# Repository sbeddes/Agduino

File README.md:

# Agduino
A compact root module system to use with an Arduino Nano, Screw Terminal, RTC 3231, and SD Card module for simple datalogging.

Primarily for use with the Arduino Nano Family. 

The Logger library provides easy device fusion for datalogging using the RTC and SD libraries. While this library can be used for any Arduino IDE cabale board, it was designed to be used with the Arduino Nano family.

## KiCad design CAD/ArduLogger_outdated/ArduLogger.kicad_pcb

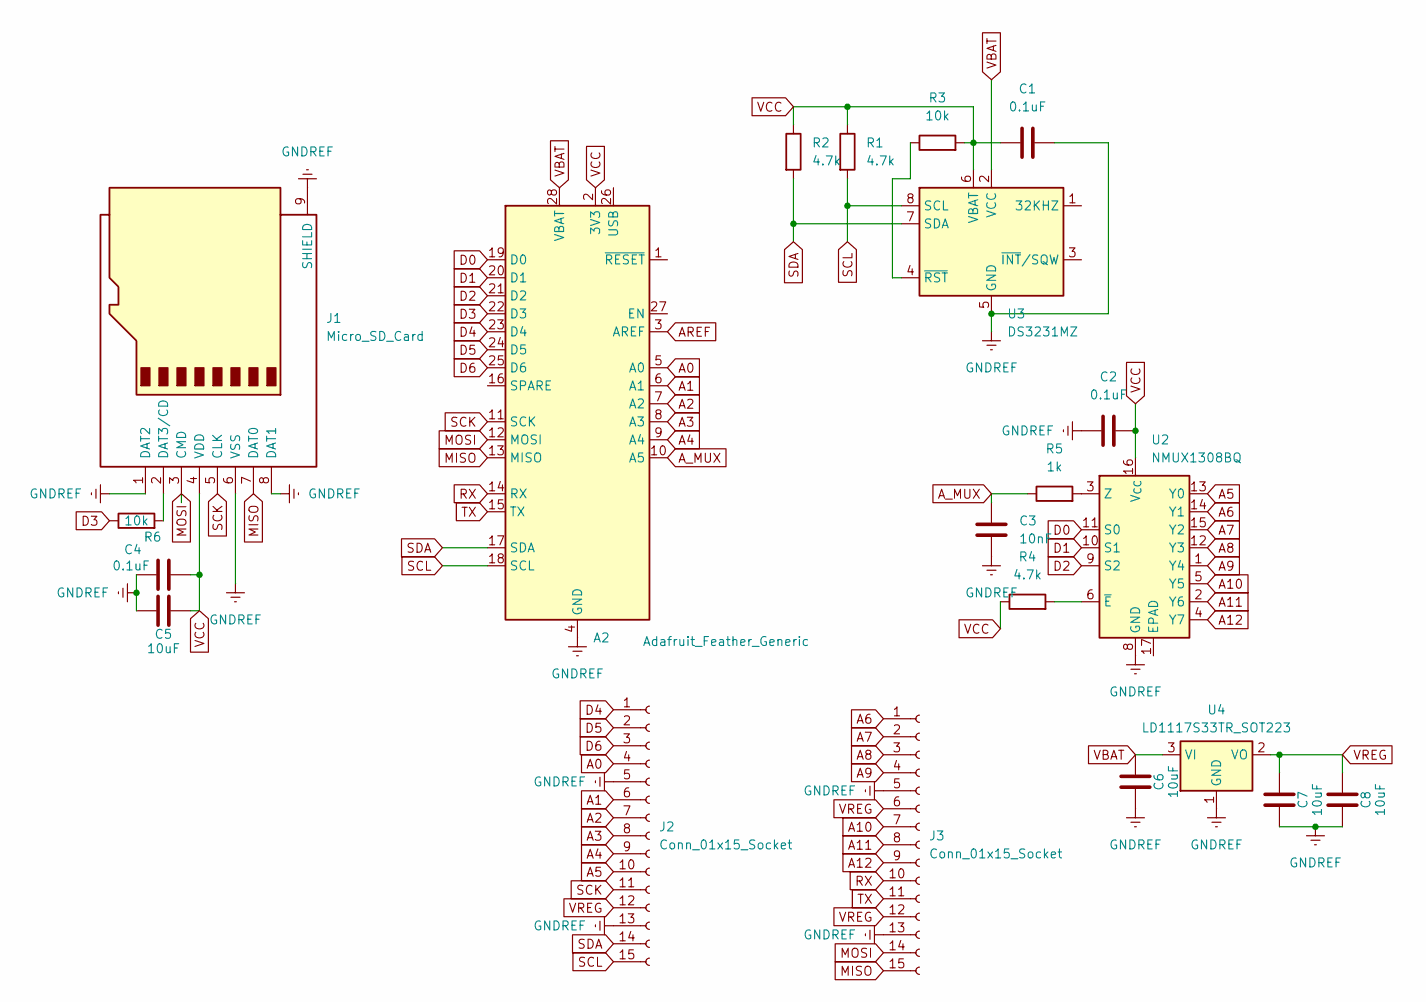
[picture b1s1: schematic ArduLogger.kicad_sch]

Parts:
A2: Adafruit_Feather_Generic; Adafruit_Feather
C1, C2, C4: 0.1uF; C_0603_1608Metric
C3: 10nF; C_0603_1608Metric
C5, C6, C7, C8: 10uF; C_0603_1608Metric
J1: Micro_SD_Card; microSD_HC_Wuerth_693072010801
J2, J3: Conn_01x15_Socket; PhoenixContact_MSTBVA_2,5_15-G-5,08_1x15_P5.08mm_Vertical
R1, R2, R4: 4.7k; R_0603_1608Metric
R3, R6: 10k; R_0603_1608Metric
R5: 1k; R_0603_1608Metric
U2: NMUX1308BQ; DHVQFN-16-1EP_2.5x3.5mm_P0.5mm_EP1x2mm
U3: DS3231MZ; SOIC-8_3.9x4.9mm_P1.27mm
U4: LD1117S33TR_SOT223; SOT-223-3_TabPin2

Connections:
A0: A2.5 (A0), J2.4
A1: A2.6 (A1), J2.6
A2: A2.7 (A2), J2.7
A3: A2.8 (A3), J2.8
A4: A2.9 (A4), J2.9
A5: J2.10, U2.13 (Y0)
A6: J3.1, U2.14 (Y1)
A7: J3.2, U2.15 (Y2)
A8: J3.3, U2.12 (Y3)
A9: J3.4, U2.1 (Y4)
A10: J3.7, U2.5 (Y5)
A11: J3.8, U2.2 (Y6)
A12: J3.9, U2.4 (Y7)
AREF: A2.3 (AREF)
A_MUX: A2.10 (A5), C3.1, R5.1
D0: A2.19 (D0), U2.11 (S0)
D1: A2.20 (D1), U2.10 (S1)
D2: A2.21 (D2), U2.9 (S2)
D3: A2.22 (D3), R6.1
D4: A2.23 (D4), J2.1
D5: A2.24 (D5), J2.2
D6: A2.25 (D6), J2.3
GNDREF: A2.4 (GND), C1.2, C2.1, C3.2, C4.1, C5.1, C6.1, C7.1, C8.1, J1.1 (DAT2), J1.6 (VSS), J1.8 (DAT1), J1.9 (SHIELD), J2.5, J2.13, J3.5, J3.13, U2.8 (GND), U3.5 (GND), U4.1 (GND)
MISO: A2.13 (MISO), J1.7 (DAT0), J3.15
MOSI: A2.12 (MOSI), J1.3 (CMD), J3.14
unnamed: J1.2 (DAT3/CD), R6.2
unnamed: R5.2, U2.3 (Z)
unnamed: R4.2, U2.6 (~E)
unnamed: R3.1, U3.4 (~RST)
RX: A2.14 (RX), J3.10
SCK: A2.11 (SCK), J1.5 (CLK), J2.11
SCL: A2.18 (SCL), J2.15, R1.2, U3.8 (SCL)
SDA: A2.17 (SDA), J2.14, R2.2, U3.7 (SDA)
TX: A2.15 (TX), J3.11
VBAT: A2.28 (VBAT), C6.2, U3.2 (VCC), U4.3 (VI)
VCC: A2.2 (3V3), C1.1, C2.2, C4.2, C5.2, J1.4 (VDD), R1.1, R2.1, R3.2, R4.1, U2.16 (V_{CC}), U3.6 (VBAT)
VREG: C7.2, C8.2, J2.12, J3.6, J3.12, U4.2 (VO)

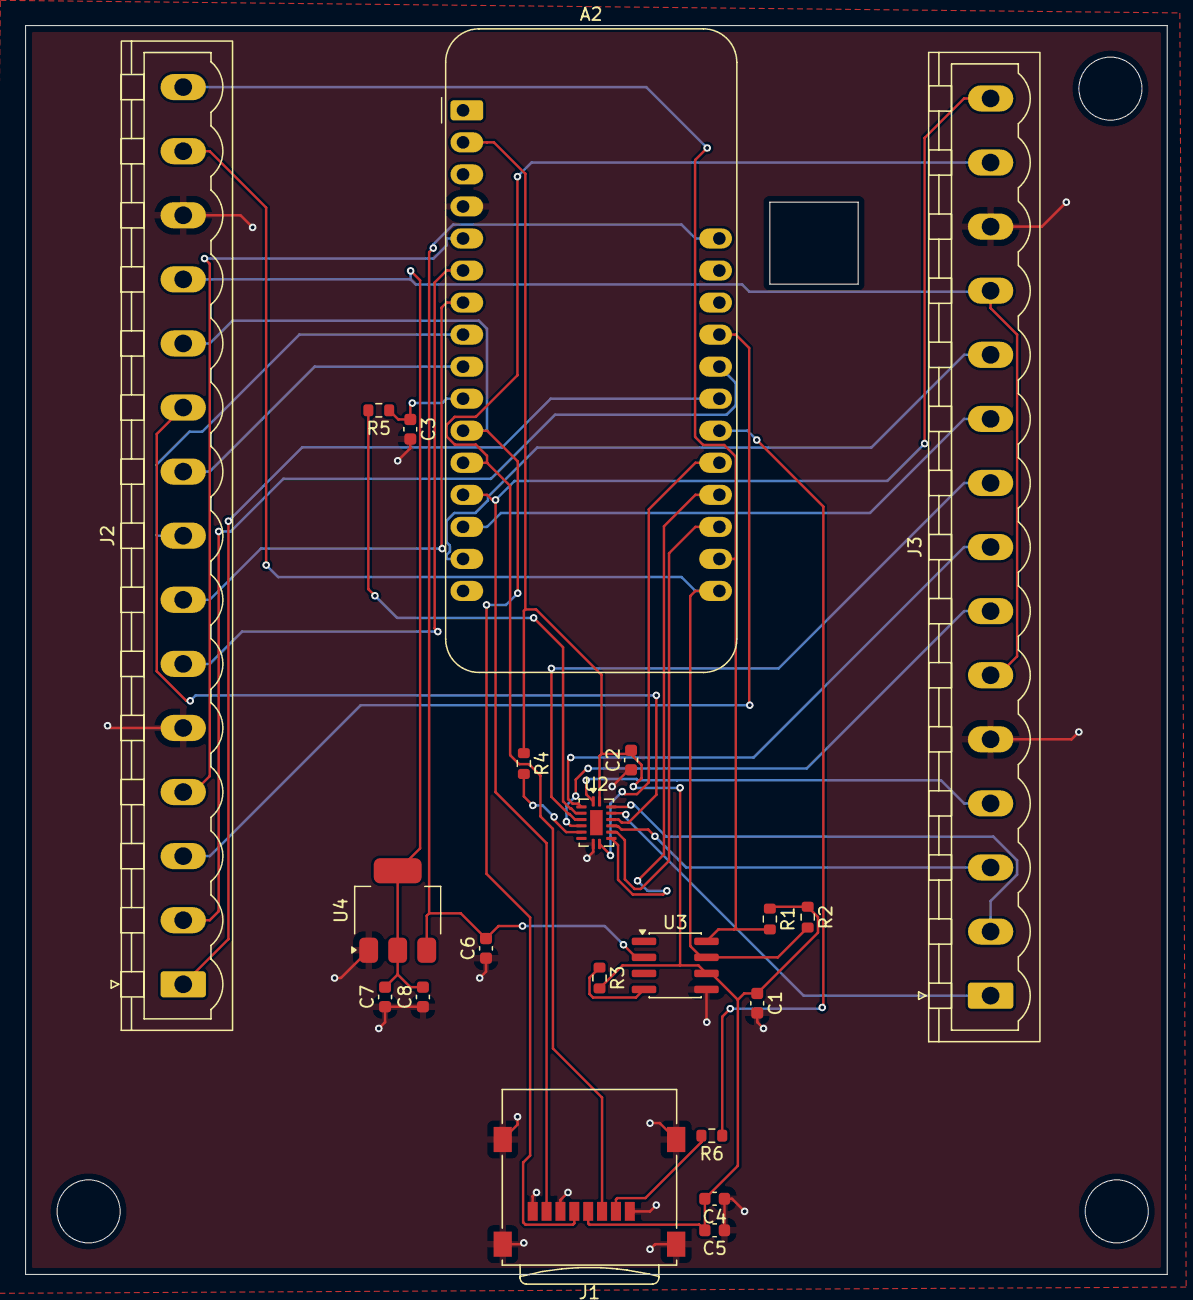
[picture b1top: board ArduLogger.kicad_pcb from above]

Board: 2 copper layers, 90.5 x 99.0 mm, 21 parts (0 on the bottom side), 36 nets.

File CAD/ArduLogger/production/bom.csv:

Designator,Footprint,Quantity,Value,LCSC Part #
A2,Adafruit_Feather,1,Adafruit_Feather_Generic,
"C1, C2, C4",0603,3,0.1uF,
C3,0603,1,10nF,
"C5, C6, C7, C8",0603,4,10uF,
J1,microSD_HC_Wuerth_693072010801,1,Micro_SD_Card,
"J2, J3","PhoenixContact_MSTBVA_2,5_15-G-5,08_1x15_P5.08mm_Vertical",2,Conn_01x15_Socket,
"R1, R2, R4",0603,3,4.7k,
"R3, R6",0603,2,10k,
R5,0603,1,1k,
U2,DHVQFN-16-1EP_2.5x3.5mm_P0.5mm_EP1x2mm,1,NMUX1308BQ,
U3,SOIC-8_3.9x4.9mm_P1.27mm,1,DS3231MZ,
U4,SOT-223-3_TabPin2,1,LD1117S33TR_SOT223,

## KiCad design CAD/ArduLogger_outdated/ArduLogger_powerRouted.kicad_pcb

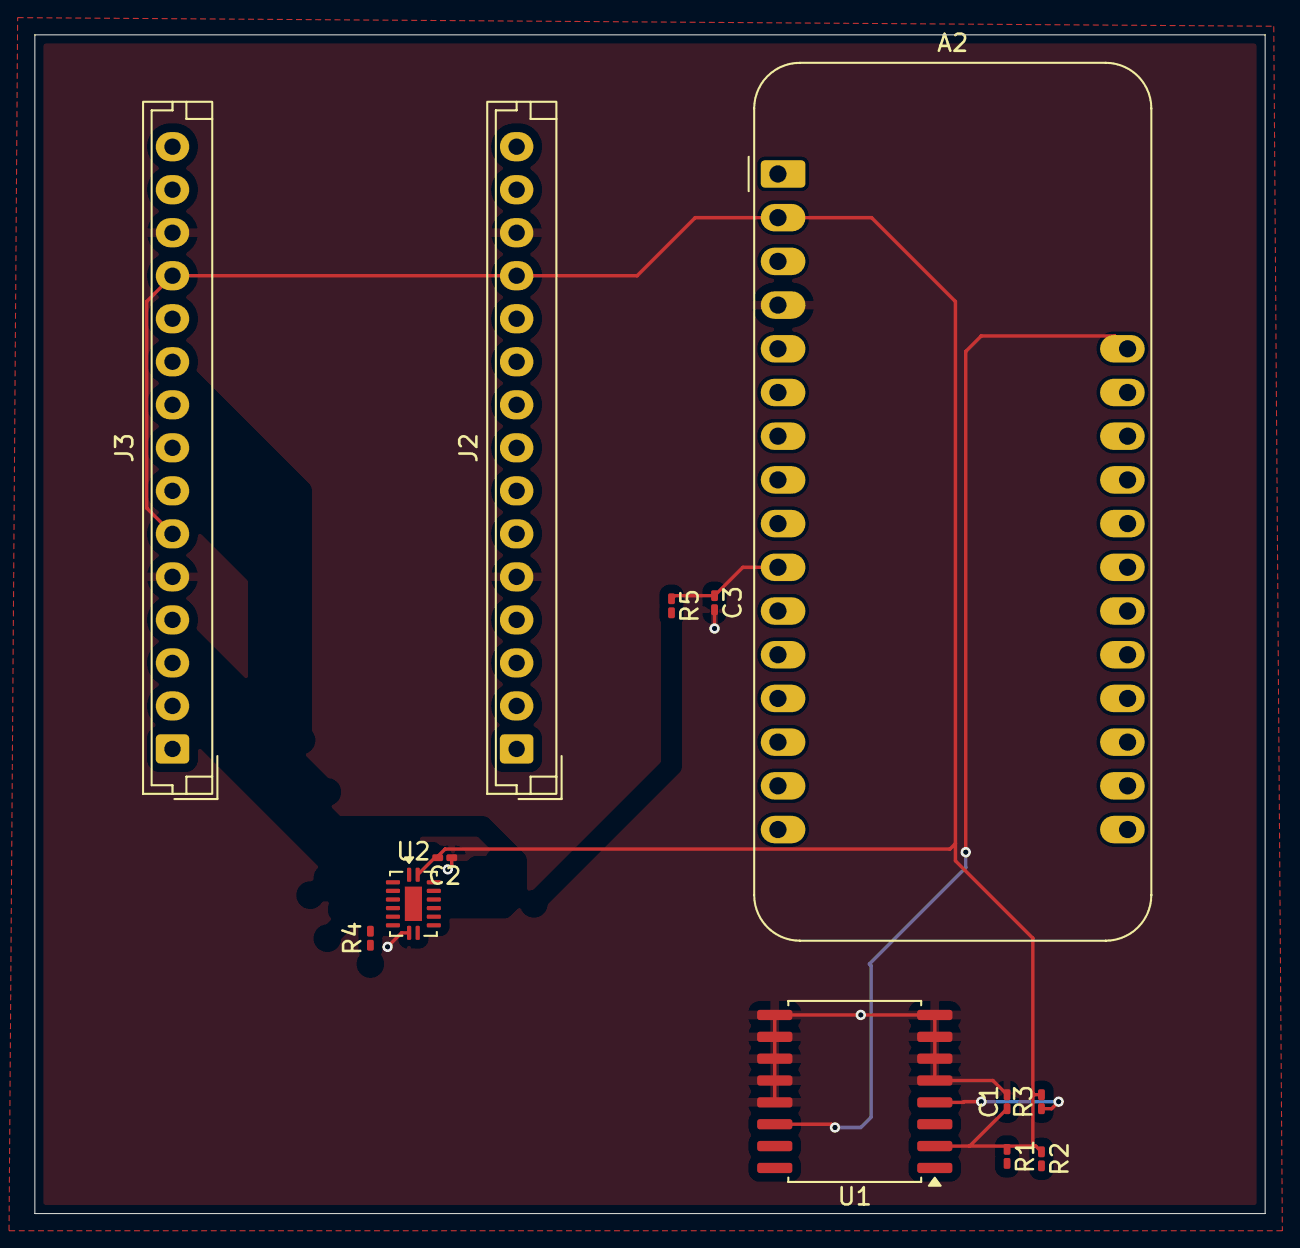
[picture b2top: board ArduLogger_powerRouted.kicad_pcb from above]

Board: 2 copper layers, 71.5 x 68.5 mm, 13 parts (0 on the bottom side), 32 nets.

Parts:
A2: Adafruit_Feather_Generic; Adafruit_Feather
C1, C2: 0.1uF; C_0201_0603Metric_Pad0.64x0.40mm_HandSolder
C3: 10nF; C_0201_0603Metric_Pad0.64x0.40mm_HandSolder
J2, J3: Conn_01x15_Socket; JST_EH_B15B-EH-A_1x15_P2.50mm_Vertical
R1, R2, R4: 4.7k; R_0201_0603Metric_Pad0.64x0.40mm_HandSolder
R3: 10k; R_0201_0603Metric_Pad0.64x0.40mm_HandSolder
R5: 100; R_0201_0603Metric_Pad0.64x0.40mm_HandSolder
U1: DS3231M; SOIC-16W_7.5x10.3mm_P1.27mm
U2: NMUX1308BQ; DHVQFN-16-1EP_2.5x3.5mm_P0.5mm_EP1x2mm

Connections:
A0: A2.5 (A0), J2.6
A1: A2.6 (A1), J2.7
A2: A2.7 (A2), J2.8
A3: A2.8 (A3), J2.9
A4: A2.9 (A4), J2.10
A5: J2.11, U2.13 (Y0)
A6: J3.2, U2.14 (Y1)
A7: J3.3, U2.15 (Y2)
A8: J3.4, U2.12 (Y3)
A9: J3.7, U2.1 (Y4)
A10: J3.8, U2.5 (Y5)
A11: J3.9, U2.2 (Y6)
A12: J3.10, U2.4 (Y7)
A_MUX: A2.10 (A5), C3.1, R5.1
D0: A2.19 (D0), U2.11 (S0)
D1: A2.20 (D1), U2.10 (S1)
D2: A2.21 (D2), U2.9 (S2)
D3: A2.22 (D3), J2.1
D4: A2.23 (D4), J2.2
D5: A2.24 (D5), J2.3
D6: A2.25 (D6), J2.4
GNDREF: A2.4 (GND), C1.2, C2.1, C3.2, J2.5, J2.13, J3.5, J3.13, U1.5 (GND), U1.6 (GND), U1.7 (GND), U1.8 (GND), U1.9 (GND), U1.10 (GND), U1.11 (GND), U1.12 (GND), U1.13 (GND), U2.8 (GND)
MISO: A2.13 (MISO), J3.15
MOSI: A2.12 (MOSI), J3.14
unnamed: A2.28 (VBAT), U1.14 (VBAT)
unnamed: R3.1, U1.4 (~RST)
unnamed: R5.2, U2.3 (Z)
unnamed: R4.2, U2.6 (~E)
SCK: A2.11 (SCK), J3.11
SCL: A2.18 (SCL), J2.15, R1.2, U1.16 (SCL)
SDA: A2.17 (SDA), J2.14, R2.2, U1.15 (SDA)
VCC: A2.2 (3V3), C1.1, C2.2, J2.12, J3.6, J3.12, R1.1, R2.1, R3.2, R4.1, U1.2 (VCC), U2.16 (V_{CC})

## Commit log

2025-05-11 Adding logger library files
2025-05-11 Logger Example Program
2025-05-11 Added bind features
2025-05-11 Adding examples and complete library
2025-05-11 Deleting redundant files
2025-05-12 Added properties file
2025-05-12 Updated library name
2025-05-23 Switched to sdFat
2025-05-23 Updated examples
2026-05-15 Adding CAD Directories
2026-05-15 First version of root module
2026-05-16 Updating rootmodule sample and adding root module v1
2026-05-17 Parts List not on PCB
2026-05-23 Adding battery voltage test.
2026-05-23 Adding regulator test
2026-05-29 Adding kicad files
2026-05-31 Added previous kicad files
2026-05-31 Adding updated kicad files
